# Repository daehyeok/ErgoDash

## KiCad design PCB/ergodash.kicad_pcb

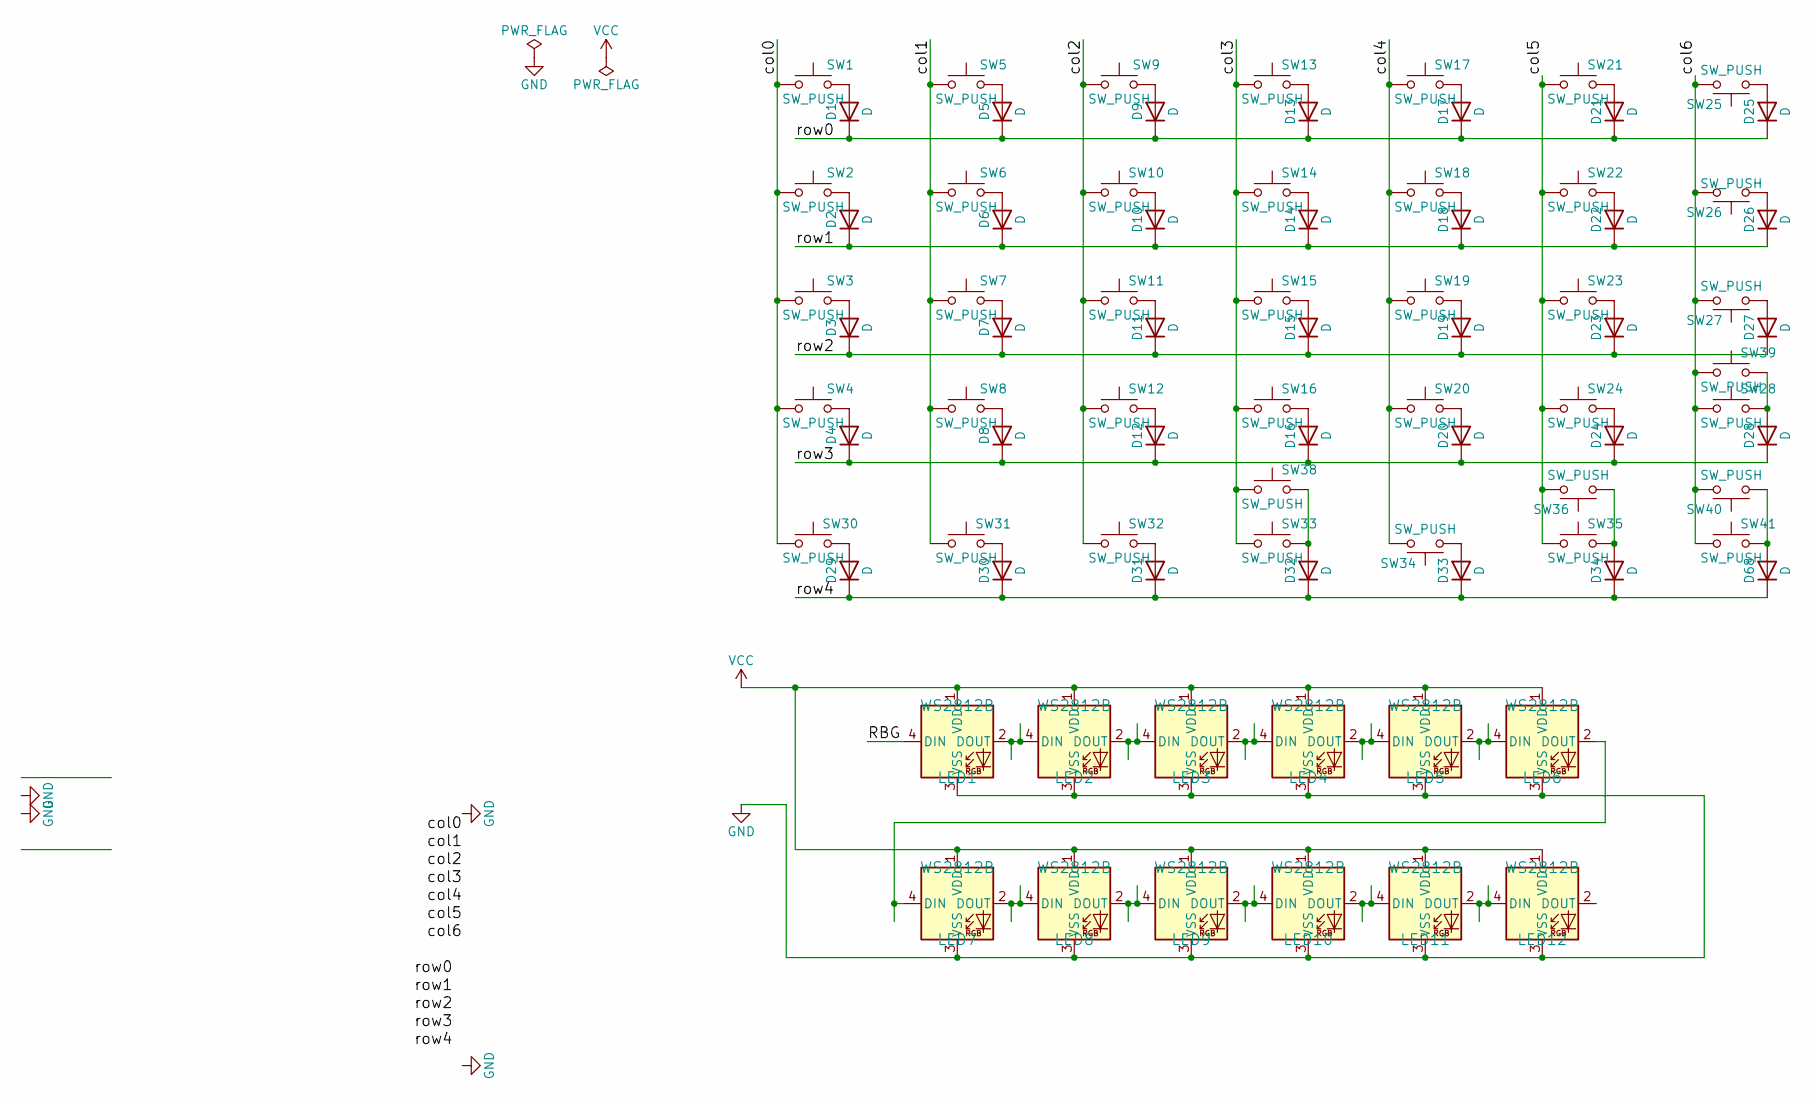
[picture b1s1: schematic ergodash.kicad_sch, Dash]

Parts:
D1, D2, D3, D4, D5, D6, D7, D8, D9, D10, D11, D12, D13, D14, D15, D16, D17, D18, D19, D20, D21, D22, D23, D24, D25, D26, D27, D28, D29, D30, D31, D32, D33, D34, D68: D; Diode_SMD_reversible
LED1, LED2, LED3, LED4, LED5, LED6, LED7, LED8, LED9, LED10, LED11, LED12: WS2812B; WS2812B-5
SW1, SW2, SW3, SW4, SW5, SW6, SW7, SW8, SW9, SW10, SW11, SW12, SW13, SW14, SW15, SW16, SW17, SW18, SW19, SW20, SW21, SW22, SW23, SW24, SW25, SW26, SW27, SW28, SW30, SW31, SW32, SW33, SW34, SW35, SW36, SW38, SW39, SW40, SW41: SW_PUSH; Kailh_socket_MX

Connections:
/RBG: LED1.4 (DIN)
/col0: SW1.1, SW2.1, SW3.1, SW4.1, SW30.1
/col1: SW5.1, SW6.1, SW7.1, SW8.1, SW31.1
/col2: SW9.1, SW10.1, SW11.1, SW12.1, SW32.1
/col3: SW13.1, SW14.1, SW15.1, SW16.1, SW33.1, SW38.1
/col4: SW17.1, SW18.1, SW19.1, SW20.1, SW34.2
/col5: SW21.1, SW22.1, SW23.1, SW24.1, SW35.1, SW36.2
/col6: SW25.2, SW26.2, SW27.2, SW28.1, SW39.1, SW40.2, SW41.1
/row0: D1.1 (K), D5.1 (K), D9.1 (K), D13.1 (K), D17.1 (K), D21.1 (K), D25.1 (K)
/row1: D2.1 (K), D6.1 (K), D10.1 (K), D14.1 (K), D18.1 (K), D22.1 (K), D26.1 (K)
/row2: D3.1 (K), D7.1 (K), D11.1 (K), D15.1 (K), D19.1 (K), D23.1 (K), D27.1 (K)
/row3: D4.1 (K), D8.1 (K), D12.1 (K), D16.1 (K), D20.1 (K), D24.1 (K), D28.1 (K)
/row4: D29.1 (K), D30.1 (K), D31.1 (K), D32.1 (K), D33.1 (K), D34.1 (K), D68.1 (K)
GND: LED1.3 (VSS), LED2.3 (VSS), LED3.3 (VSS), LED4.3 (VSS), LED5.3 (VSS), LED6.3 (VSS), LED7.3 (VSS), LED8.3 (VSS), LED9.3 (VSS), LED10.3 (VSS), LED11.3 (VSS), LED12.3 (VSS)
unnamed: D1.2 (A), SW1.2
unnamed: D2.2 (A), SW2.2
unnamed: D3.2 (A), SW3.2
unnamed: D4.2 (A), SW4.2
unnamed: D5.2 (A), SW5.2
unnamed: D6.2 (A), SW6.2
unnamed: D7.2 (A), SW7.2
unnamed: D8.2 (A), SW8.2
unnamed: D9.2 (A), SW9.2
unnamed: D10.2 (A), SW10.2
unnamed: D11.2 (A), SW11.2
unnamed: D12.2 (A), SW12.2
unnamed: D13.2 (A), SW13.2
unnamed: D14.2 (A), SW14.2
unnamed: D15.2 (A), SW15.2
unnamed: D16.2 (A), SW16.2
unnamed: D17.2 (A), SW17.2
unnamed: D18.2 (A), SW18.2
unnamed: D19.2 (A), SW19.2
unnamed: D20.2 (A), SW20.2
unnamed: D21.2 (A), SW21.2
unnamed: D22.2 (A), SW22.2
unnamed: D23.2 (A), SW23.2
unnamed: D24.2 (A), SW24.2
unnamed: D25.2 (A), SW25.1
unnamed: D26.2 (A), SW26.1
unnamed: D27.2 (A), SW27.1
unnamed: D28.2 (A), SW28.2, SW39.2
unnamed: D29.2 (A), SW30.2
unnamed: D30.2 (A), SW31.2
unnamed: D31.2 (A), SW32.2
unnamed: D32.2 (A), SW33.2, SW38.2
unnamed: D33.2 (A), SW34.1
unnamed: D34.2 (A), SW35.2, SW36.1
unnamed: D68.2 (A), SW40.1, SW41.2
unnamed: LED1.2 (DOUT), LED2.4 (DIN)
unnamed: LED2.2 (DOUT), LED3.4 (DIN)
unnamed: LED3.2 (DOUT), LED4.4 (DIN)
unnamed: LED4.2 (DOUT), LED5.4 (DIN)
unnamed: LED5.2 (DOUT), LED6.4 (DIN)
unnamed: LED6.2 (DOUT), LED7.4 (DIN)
unnamed: LED7.2 (DOUT), LED8.4 (DIN)
unnamed: LED8.2 (DOUT), LED9.4 (DIN)
unnamed: LED10.2 (DOUT), LED11.4 (DIN)
unnamed: LED9.2 (DOUT), LED10.4 (DIN)
unnamed: LED11.2 (DOUT), LED12.4 (DIN)
VCC: LED1.1 (VDD), LED2.1 (VDD), LED3.1 (VDD), LED4.1 (VDD), LED5.1 (VDD), LED6.1 (VDD), LED7.1 (VDD), LED8.1 (VDD), LED9.1 (VDD), LED10.1 (VDD), LED11.1 (VDD), LED12.1 (VDD)

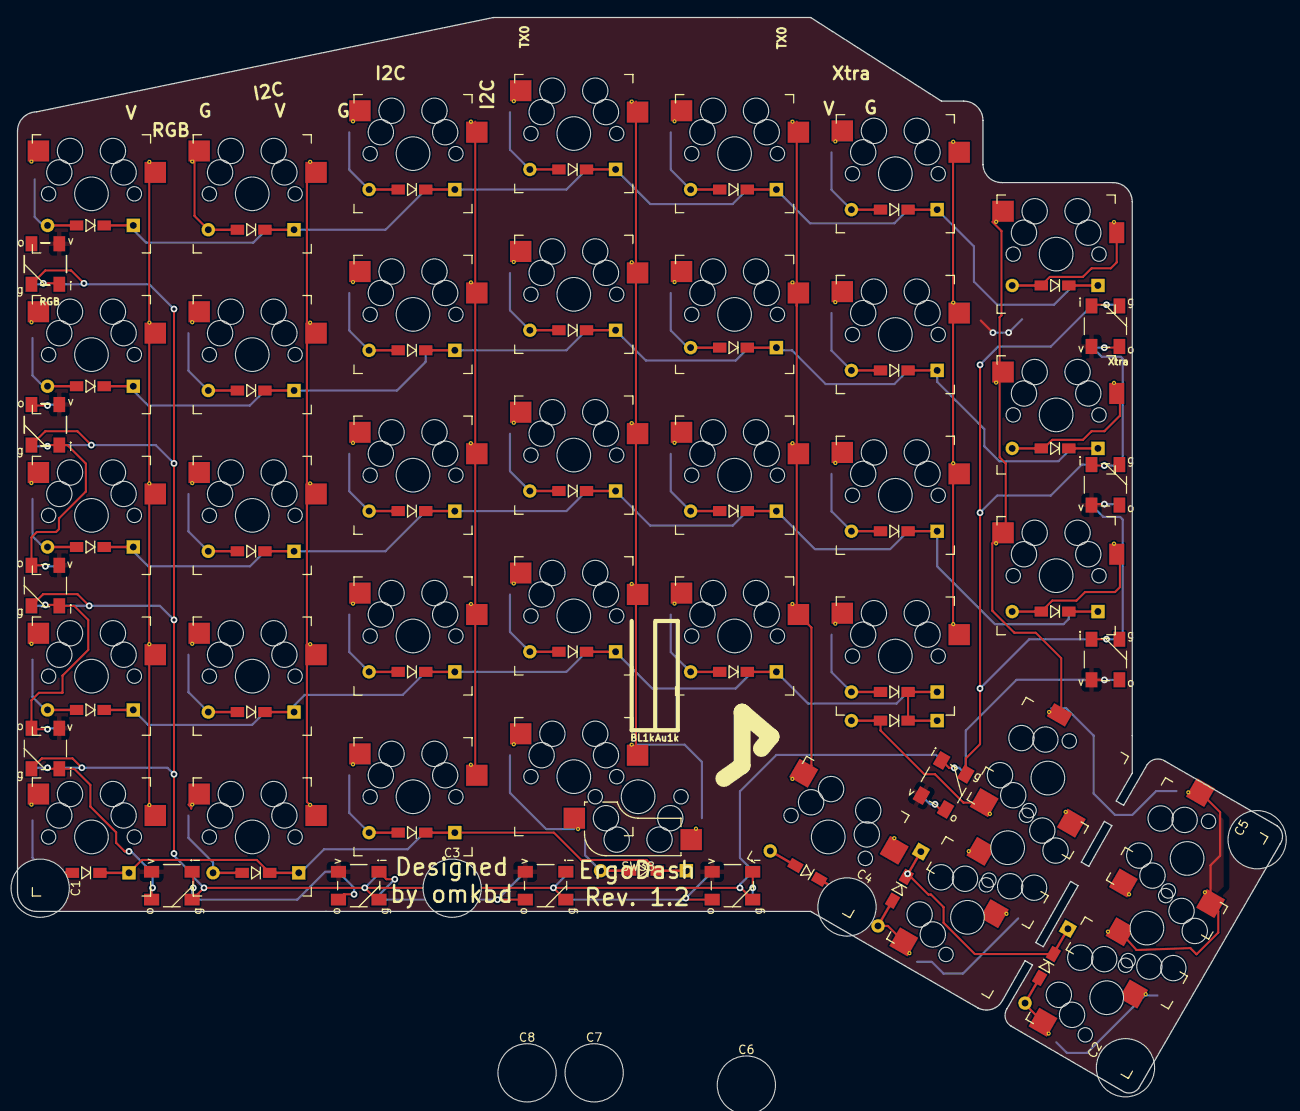
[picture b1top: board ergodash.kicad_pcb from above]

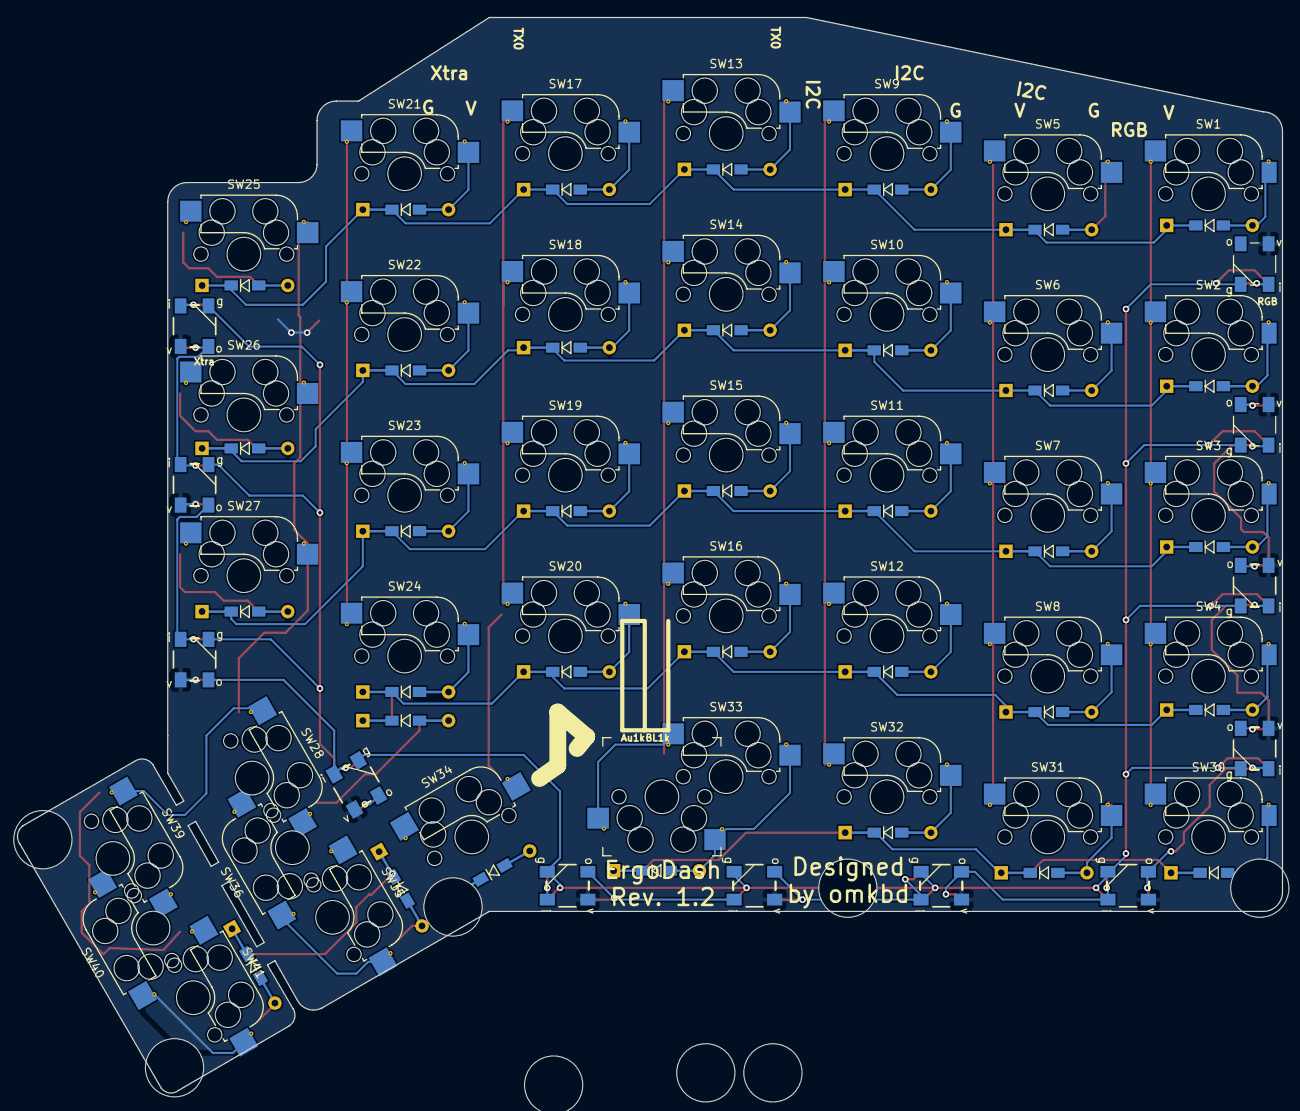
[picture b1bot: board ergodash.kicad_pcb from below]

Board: 2 copper layers, 149.9 x 127.4 mm, 94 parts (13 on the bottom side), 60 nets.

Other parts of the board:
C1, C2, C3, C4, C5, C6, C7, C8: MountingHole; Plate_MountingHole_cut
